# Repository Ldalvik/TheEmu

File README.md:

# TheEmu
Arduino servo crane thing

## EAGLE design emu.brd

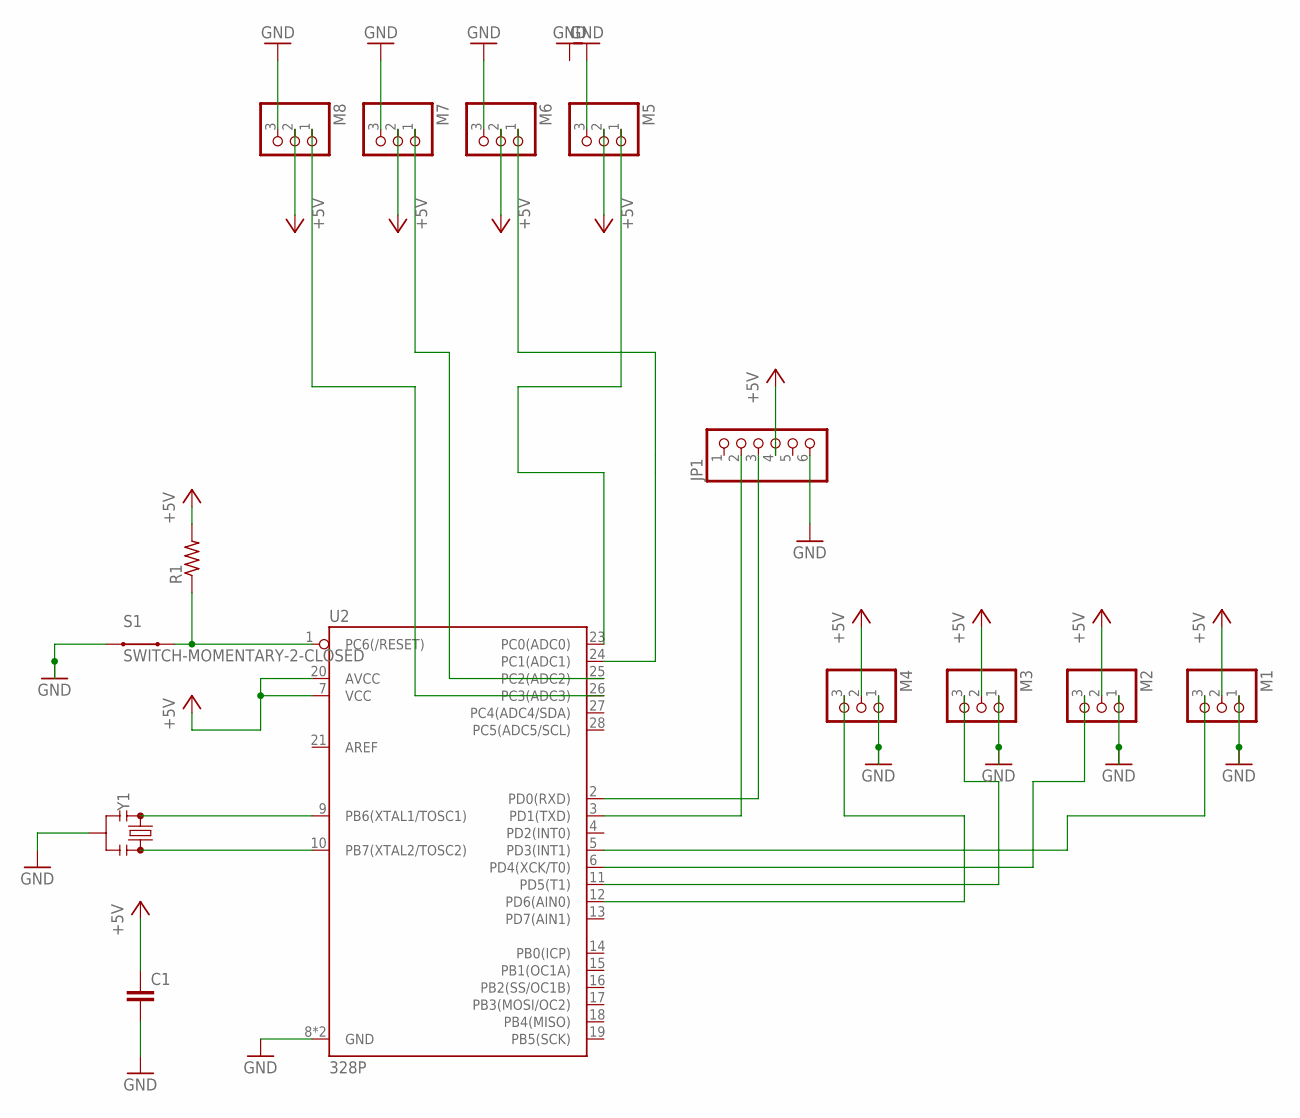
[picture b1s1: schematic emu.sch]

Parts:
C1: C2.5/4; C2.5-4
JP1: PINHD-1X6; 1X06
M1, M2, M3, M4, M5, M6, M7, M8: PINHD-1X3; 1X03
R1: R-US_0204/7; 0204/7
S1: SWITCH-MOMENTARY-2-CLOSED; TACTILE-PTH-12MM
U2: 328P; DIP28
Y1: RESONATORPTH-7.6X3.8; RESONATOR-PTH-7.6X3.8

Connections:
+5V: C1.1, JP1.4, M1.2, M2.2, M3.2, M4.2, M5.2, M6.2, M7.2, M8.2, R1.2, U2.7 (VCC), U2.20 (AVCC)
GND: C1.2, JP1.6, M1.1, M2.1, M3.1, M4.1, M5.3, M6.3, M7.3, M8.3, S1.1, U2.8 (GND), U2.22 (GND), Y1.2
unnamed: M5.1, U2.23 (PC0(ADC0))
unnamed: M6.1, U2.24 (PC1(ADC1))
unnamed: M7.1, U2.25 (PC2(ADC2))
unnamed: M8.1, U2.26 (PC3(ADC3))
unnamed: M4.3, U2.12 (PD6(AIN0))
unnamed: M3.3, U2.11 (PD5(T1))
unnamed: M2.3, U2.6 (PD4(XCK/T0))
unnamed: M1.3, U2.5 (PD3(INT1))
unnamed: R1.1, S1.3 (2), U2.1 (PC6(/RESET))
unnamed: JP1.3, U2.2 (PD0(RXD))
unnamed: JP1.2, U2.3 (PD1(TXD))
unnamed: U2.9 (PB6(XTAL1/TOSC1)), Y1.1
unnamed: U2.10 (PB7(XTAL2/TOSC2)), Y1.3

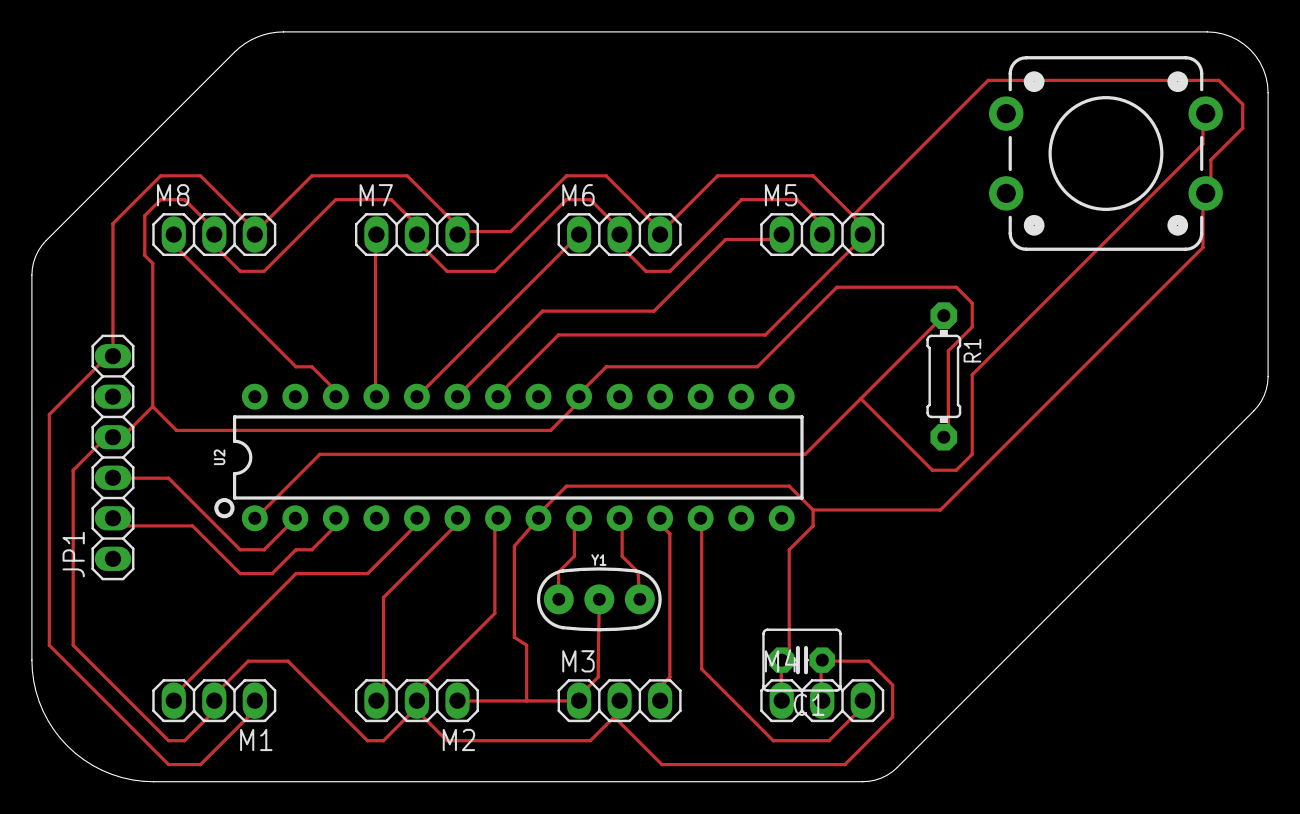
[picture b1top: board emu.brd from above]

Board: 2 copper layers, 77.5 x 47.0 mm, 14 parts (0 on the bottom side), 15 nets.

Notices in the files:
parts and their libraries:
SparkFun-IC-Microcontroller: Licensing: Creative Commons ShareAlike 4.0 International - https://creativecommons.org/licenses/by-sa/4.0
